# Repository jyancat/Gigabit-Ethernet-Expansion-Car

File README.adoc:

= USB-C to Gigabit Ethernet for Framework Laptop

This repo is for the Gigabit Ethernet expansion card for the Framework Laptop.

Read about the Framework Laptop https://frame.work[at its home page]
and 
https://medium.com/i-tried-that/framework-laptop-saving-the-planet-one-sustainable-laptop-at-a-time-8a4cb71e54a7[at this review site].

Framework said they would build an Ethernet card, but that seems to have stalled out
as they are busy making laptops.

Read about this independent Ethernet Expansion Card project
https://community.frame.work/t/ethernet-expansion-card/8752[here].

Read how Framework is opening up the marketplace to indie vendors
(like this project, perhaps) 
https://community.frame.work/t/announcing-the-framework-marketplace/8975[here].

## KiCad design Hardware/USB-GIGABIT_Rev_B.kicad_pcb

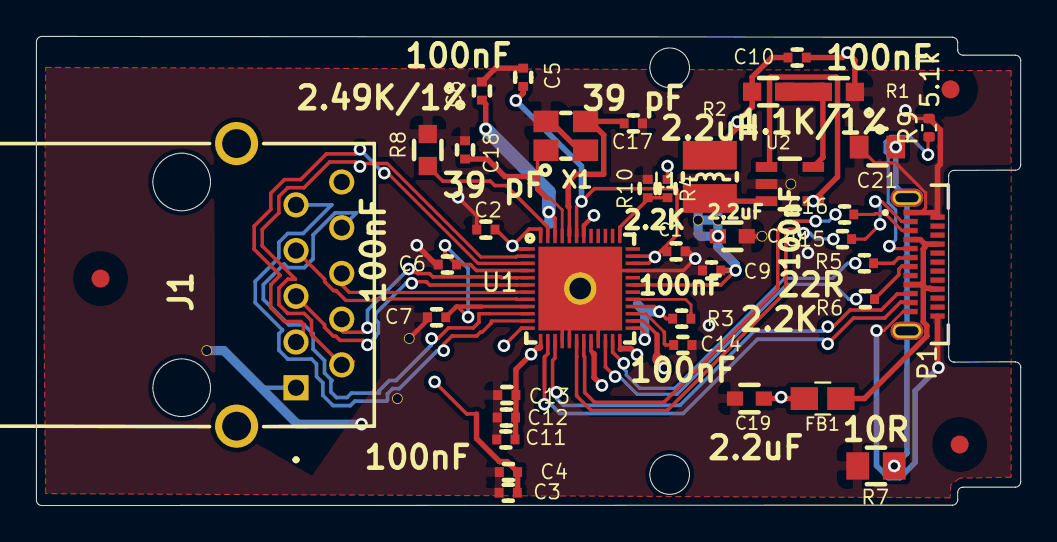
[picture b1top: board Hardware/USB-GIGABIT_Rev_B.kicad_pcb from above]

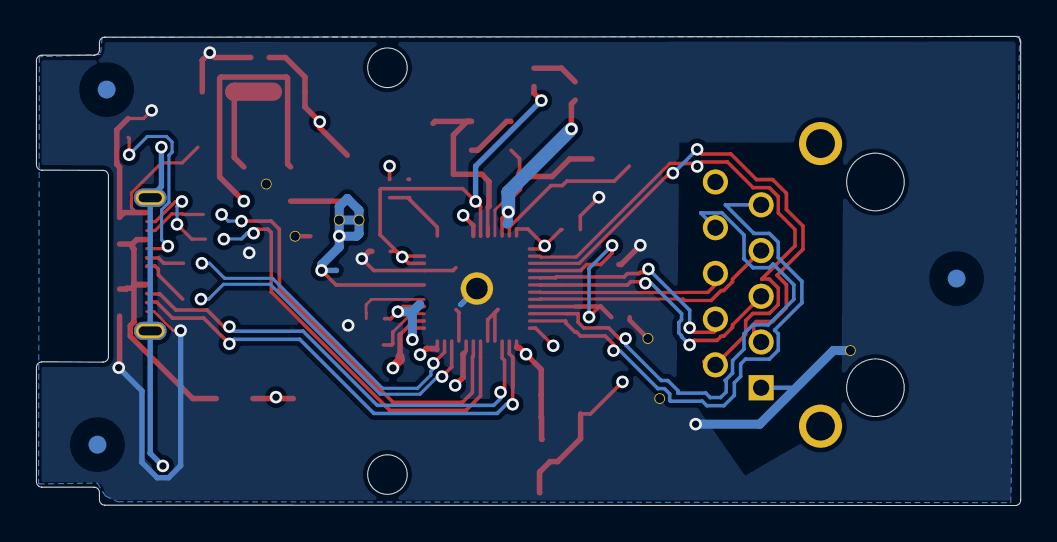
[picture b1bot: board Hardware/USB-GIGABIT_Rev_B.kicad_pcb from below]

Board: 4 copper layers, 54.7 x 26.1 mm, 51 parts (3 on the bottom side), 33 nets.

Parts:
 : Val**; Fiducial1x3_transp
 #2: Fiducial1x3_transp
 #3,  #4,  #5,  #6,  #7: via_0.5_0.6
C1, C2, C3, C4, C5, C6, C7, C8, C9, C10, C11, C12, C13, C14, C15, C16: 100nF; C_0402_5MIL_DWS
C17, C18: 39 pF; C_0402_5MIL_DWS
C19, C20: 2.2uF; C_0603_5MIL_DWS
C21: 100nF/50V; C_0805_5MIL_DWS
FB1: FB0805; L_0805_5MIL_DWS
H1: MountingHole_2.2mm_M2
H2: MountingHole; MountingHole_2.2mm_M2
J1: 2301994-5; 23019945
L1: 2.2uH; CD32
P1: USB_C_Plug; GCT_USB4155-03-C_REVA
R1, R2: 1.1K/1%; R_0603_5MIL_DWS
R3, R4: 2.2K; R_0402_5MIL_DWS
R5, R6: 22R; R_0402_5MIL_DWS
R7: 10R; R_0805_5MIL_DWS
R8: 2.49K/1%; R_0603_5MIL_DWS
R9: 5.1k; R_0402_1005Metric
R10: dnp; R_0402_5MIL_DWS
Ref**: Val**; Fiducial1x3_transp
Ref**#2, Ref**#3, Ref**#4: Val**; Fiducial1x3_transp
U1: RTL8153VCCG; QFN48-6x6mm-OLIMEX_V2
U2: SY8089AAAC(SOT23-5); SOT-23-5
X1: SMD РЕЗ. 3225 25 Mhz 20 pf 20ppm 4p; TSX-3.2x2.5mm_GND(4)

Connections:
+3V3: C1.1, C2.2, C3.2, C4.2, C5.2, J1.13, R3.2, R4.1, U1.1, U1.12, U1.25, U1.28, U1.34, U1.35, U1.43, U1.48
/M0_N: J1.3, U1.3
/M0_P: J1.2, U1.2
/M1_N: J1.5, U1.6
/M1_P: J1.4, U1.5
/M2_N: J1.7, U1.8
/M2_P: J1.6, U1.7
/M3_N: J1.12, U1.11
/M3_P: J1.8, U1.10
/U2_N: R6.1, U1.22
/U2_P: R5.1, U1.23
/U3TX_N: C16.1, U1.19
/U3TX_P: C15.1, U1.18
/V12: #3.1, #4.1, C6.2, C7.2, C8.2, C9.2, C10.2, C11.2, C12.2, C13.2, C20.1, L1.2, R2.1, U1.4, U1.9, U1.13, U1.20, U1.24, U1.31, U1.42, U1.46
GND: #5.1, #6.1, #7.1, C1.2, C2.1, C3.1, C4.1, C5.1, C6.1, C7.1, C8.1, C9.1, C10.1, C11.1, C12.1, C13.1, C14.2, C17.1, C18.2, C19.2, C20.2, C21.2, J1.1, P1.A1, P1.A12, P1.B1, P1.B12, R1.2, R7.2, R8.2, R9.2, R10.1, U1.16, U1.17, U1.21, U1.33, U1.49, U2.2, X1.2, X1.4
unnamed: C14.1, U1.27
unnamed: C17.2, U1.44, X1.3
unnamed: C18.1, U1.45, X1.1
unnamed: C19.1, FB1.2, U1.26, U2.1, U2.4
unnamed: C21.1, P1.S1, R7.1
unnamed: L1.1, U2.3
unnamed: P1.A5, R9.1
unnamed: R1.1, R2.2, U2.5
unnamed: R3.1, U1.29
unnamed: R8.1, U1.47
unnamed: R4.2, R10.2, U1.37
U2D_N: P1.A7, R6.2
U2D_P: P1.A6, R5.2
U3SRX_N: P1.A10, U1.15
U3SRX_P: P1.A11, U1.14
U3STX_N: C16.2, P1.A3
U3STX_P: C15.2, P1.A2
VBUS: FB1.1, P1.A4, P1.A9, P1.B4, P1.B9

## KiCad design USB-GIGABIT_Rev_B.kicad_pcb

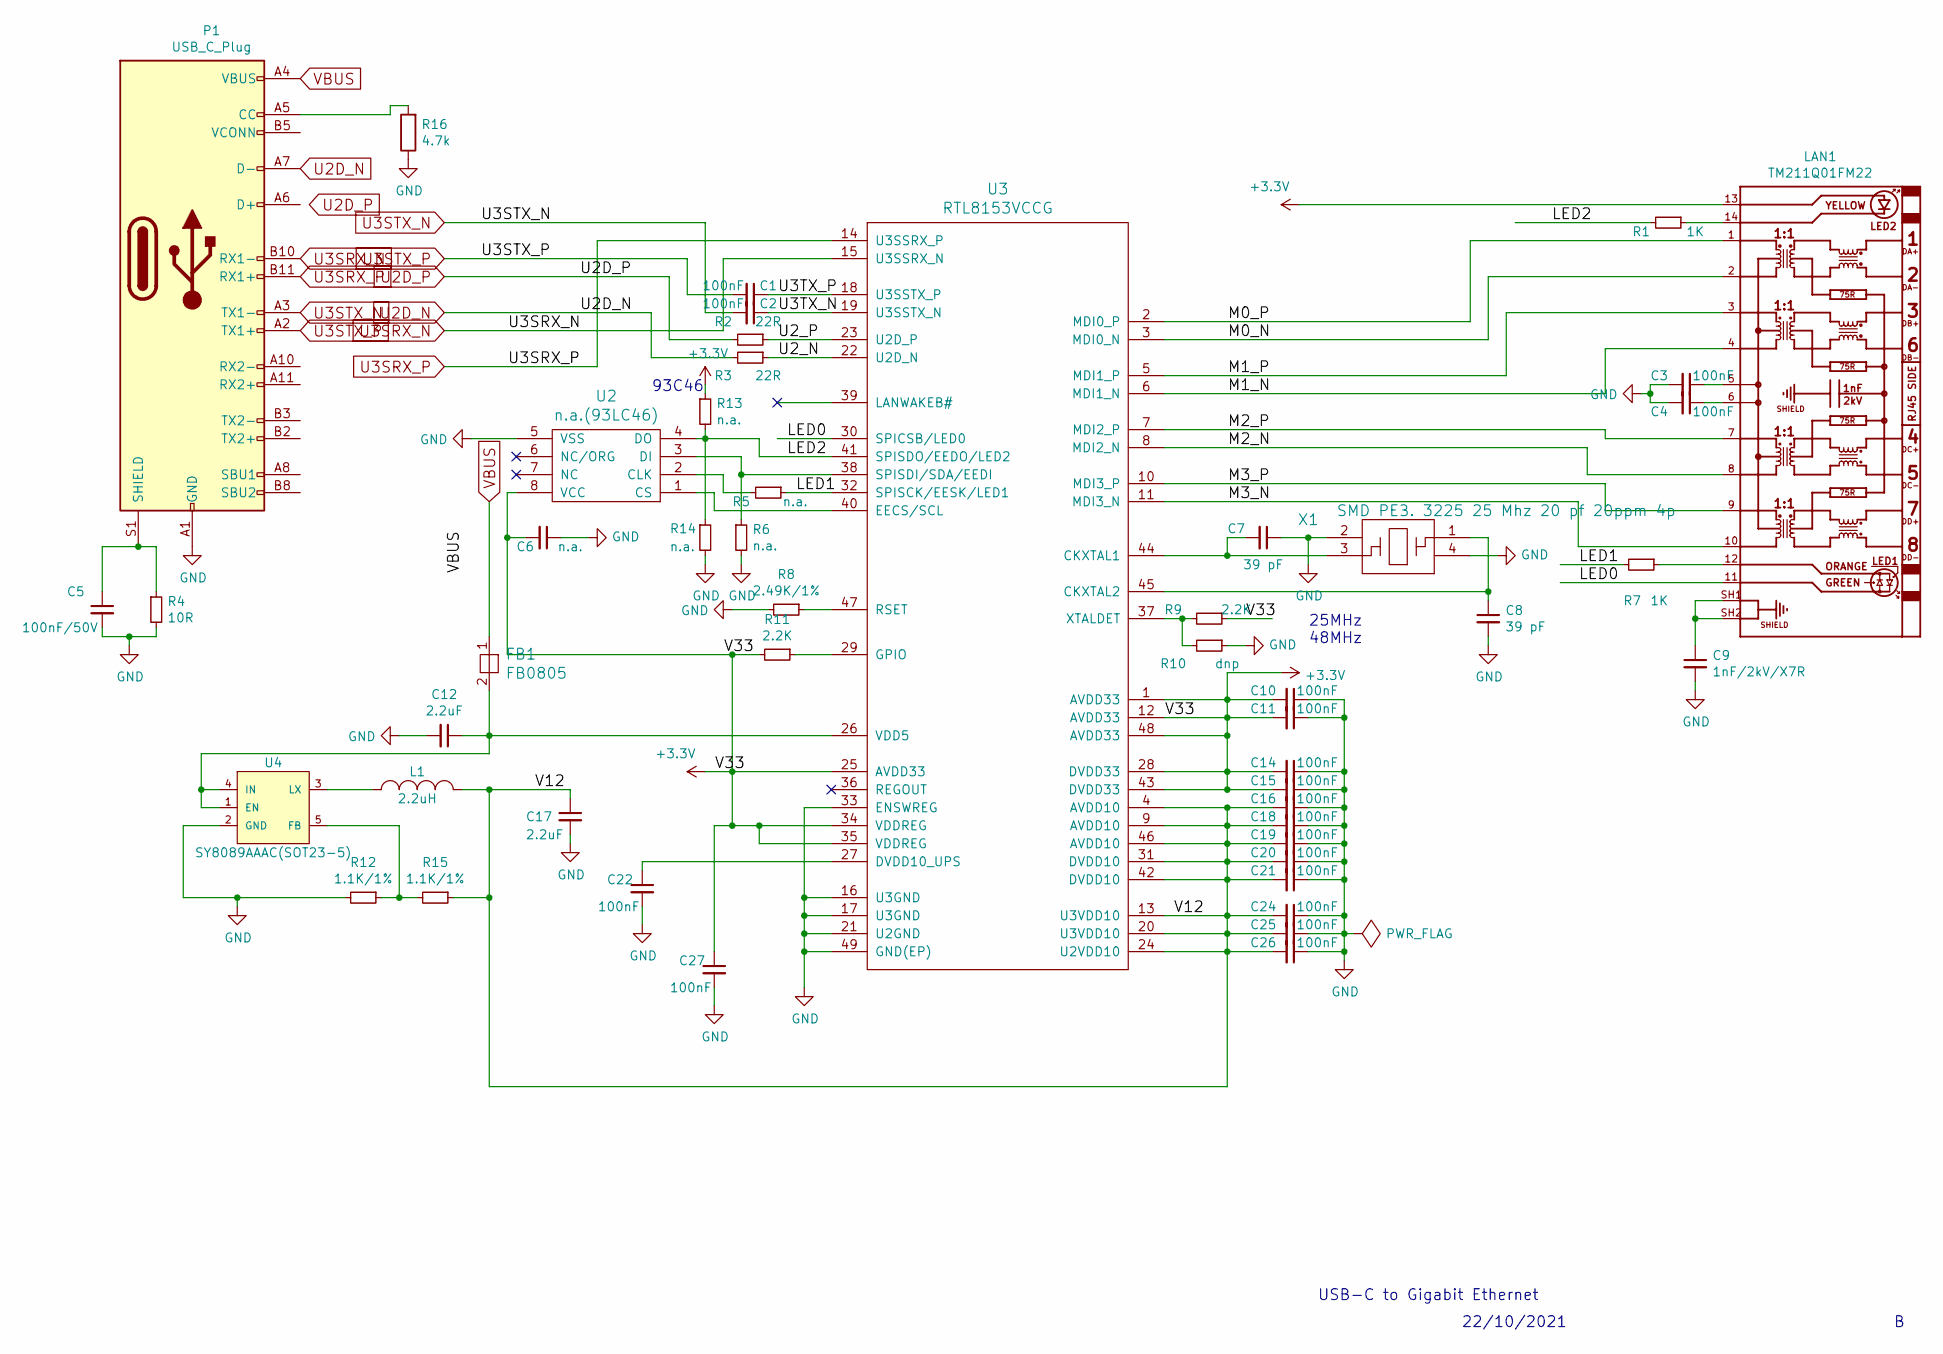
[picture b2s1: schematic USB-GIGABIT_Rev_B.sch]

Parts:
C1, C2, C10, C11, C14, C15, C16, C18, C19, C20, C21, C22, C24, C25, C26, C27: 100nF; C_0402_5MIL_DWS
C3, C4: 100nF; C_0805_5MIL_DWS
C5: 100nF/50V; C_0805_5MIL_DWS
C6: n.a.; C_0402_5MIL_DWS
C7, C8: 39 pF; C_0402_5MIL_DWS
C9: 1nF/2kV/X7R; C_1206_5MIL_DWS_ISO
C12, C17: 2.2uF; C_0603_5MIL_DWS
FB1: FB0805; L_0805_5MIL_DWS
L1: 2.2uH; CD32
LAN1: TM211Q01FM22
P1: USB_C_Plug
R1, R7: 1K; R_0603_5MIL_DWS
R2, R3: 22R; R_0402_5MIL_DWS
R4: 10R; R_0805_5MIL_DWS
R5, R6, R13, R14: n.a.; R_0402_5MIL_DWS
R8: 2.49K/1%; R_0603_5MIL_DWS
R9, R11: 2.2K; R_0402_5MIL_DWS
R10: dnp; R_0402_5MIL_DWS
R12, R15: 1.1K/1%; R_0603_5MIL_DWS
R16: 4.7k
U2: n.a.(93LC46); SO-8
U3: RTL8153VCCG; QFN48-6x6mm-OLIMEX_V2
U4: SY8089AAAC(SOT23-5); SOT-23-5
X1: SMD РЕЗ. 3225 25 Mhz 20 pf 20ppm 4p; TSX-3.2x2.5mm_GND(4)

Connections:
+3V3: C6.2, C10.2, C11.2, C14.2, C15.2, C27.1, LAN1.13, R9.1, R11.2, R13.1, U2.8 (VCC), U3.1 (AVDD33), U3.12 (AVDD33), U3.25 (AVDD33), U3.28 (DVDD33), U3.34 (VDDREG), U3.35 (VDDREG), U3.43 (DVDD33), U3.48 (AVDD33)
/LED0: LAN1.11, U3.30 (SPICSB/LED0)
/LED1: R5.1, R7.2, U3.32 (SPISCK/EESK/LED1)
/LED2: R1.2, R13.2, R14.1, U2.4 (DO), U3.41 (SPISDO/EEDO/LED2)
/M0_N: LAN1.2, U3.3 (MDI0_N)
/M0_P: LAN1.1, U3.2 (MDI0_P)
/M1_N: LAN1.4, U3.6 (MDI1_N)
/M1_P: LAN1.3, U3.5 (MDI1_P)
/M2_N: LAN1.8, U3.8 (MDI2_N)
/M2_P: LAN1.7, U3.7 (MDI2_P)
/M3_N: LAN1.10, U3.11 (MDI3_N)
/M3_P: LAN1.9, U3.10 (MDI3_P)
/U2_N: R3.1, U3.22 (U2D_N)
/U2_P: R2.1, U3.23 (U2D_P)
/U3TX_N: C2.1, U3.19 (U3SSTX_N)
/U3TX_P: C1.1, U3.18 (U3SSTX_P)
/V12: C16.2, C17.1, C18.2, C19.2, C20.2, C21.2, C24.2, C25.2, C26.2, L1.2, R15.1, U3.4 (AVDD10), U3.9 (AVDD10), U3.13 (U3VDD10), U3.20 (U3VDD10), U3.24 (U2VDD10), U3.31 (DVDD10), U3.42 (DVDD10), U3.46 (AVDD10)
unnamed: C3.1, LAN1.5
unnamed: C4.1, LAN1.6
unnamed: C5.1, P1.S1 (SHIELD), R4.1
unnamed: C7.2, U3.44 (CKXTAL1), X1.3
unnamed: C8.1, U3.45 (CKXTAL2), X1.1
unnamed: C9.1, LAN1.SH1, LAN1.SH2
unnamed: C12.1, FB1.2, U3.26 (VDD5), U4.1 (EN), U4.4 (IN)
unnamed: C22.1, U3.27 (DVDD10_UPS)
unnamed: L1.1, U4.3 (LX)
unnamed: LAN1.12, R7.1
unnamed: LAN1.14, R1.1
unnamed: R5.2, U2.2 (CLK)
unnamed: R6.1, U2.3 (DI), U3.38 (SPISDI/SDA/EEDI)
unnamed: R8.1, U3.47 (RSET)
unnamed: R9.2, R10.2, U3.37 (XTALDET)
unnamed: R11.1, U3.29 (GPIO)
unnamed: R12.1, R15.2, U4.5 (FB)
unnamed: U2.1 (CS), U3.40 (EECS/SCL)
U2D_N: P1.A7 (D-), R3.2
U2D_P: P1.A6 (D+), R2.2
U3SRX_N: P1.B10 (RX1-), U3.15 (U3SSRX_N)
U3SRX_P: P1.B11 (RX1+), U3.14 (U3SSRX_P)
U3STX_N: C2.2, P1.A3 (TX1-)
U3STX_P: C1.2, P1.A2 (TX1+)
VBUS: FB1.1, P1.A4 (VBUS), P1.A9 (VBUS), P1.B4 (VBUS), P1.B9 (VBUS)

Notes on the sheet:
93C46
25MHz 48MHz
USB-C to Gigabit Ethernet
22/10/2021

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
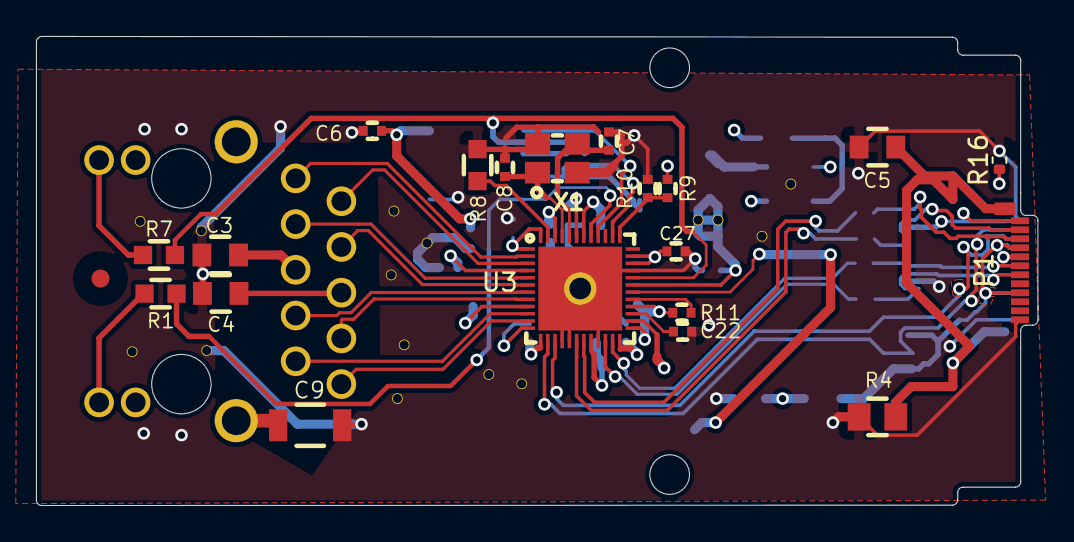
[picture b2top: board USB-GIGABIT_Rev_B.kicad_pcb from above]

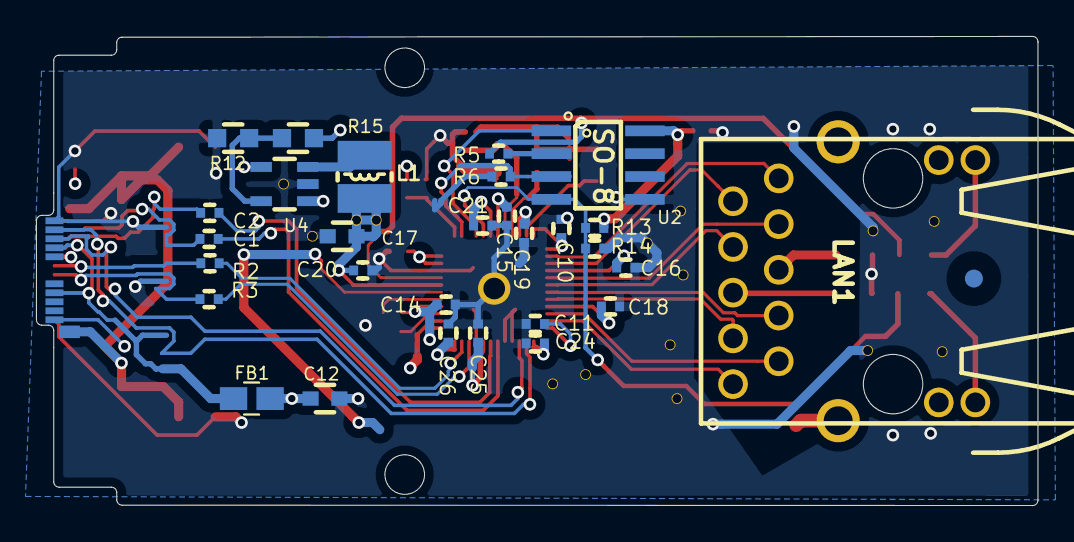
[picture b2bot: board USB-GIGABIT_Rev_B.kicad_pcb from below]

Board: 4 copper layers, 55.6 x 26.1 mm, 53 parts (30 on the bottom side), 44 nets.

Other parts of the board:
H1, H2: MountingHole; MountingHole_2.2mm_M2
Ref**: Val**; Fiducial1x3_transp
Ref**#2: Val**; Fiducial1x3_transp

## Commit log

2021-10-22 Added new files.
2021-11-22 Add a README
2021-11-22 Updated to Newest change.
2022-04-16 Added files using updated GCT connector and all components are on one side.
2022-04-16 removed old files
2022-04-16 Removed old
2022-04-16 Changed
2022-04-16 Updated Bom
